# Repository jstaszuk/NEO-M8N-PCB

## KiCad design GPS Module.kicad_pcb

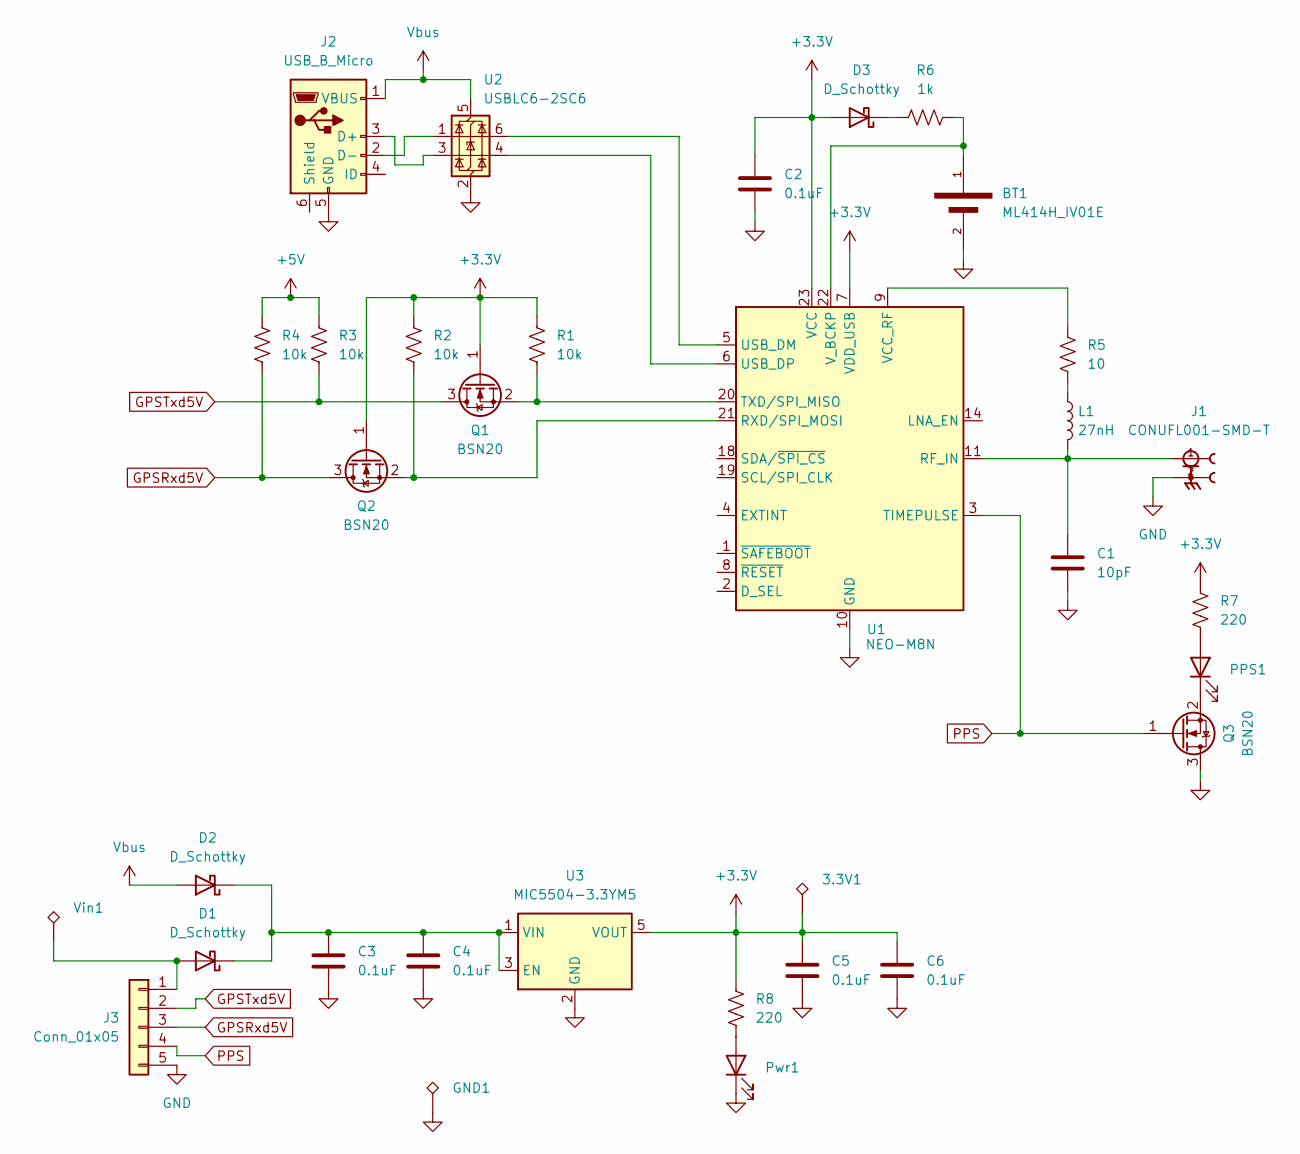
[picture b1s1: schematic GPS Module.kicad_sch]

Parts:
3.3V1: TestPoint_Alt; TestPoint_Pad_D1.0mm
BT1: ML414H_IV01E; SEIKO_ML414H_IV01E
C1: 10pF; C_0603_1608Metric; Part Number CC0603JRNPO9BN100
C2, C3, C4, C5, C6: 0.1uF; C_0603_1608Metric; Part Number CC0603KRX7R9BB104
D1, D2, D3: D_Schottky; D_0805_2012Metric; Part Number ZHCS400TA
GND1: TestPoint_Alt; TestPoint_Pad_D1.0mm
J1: CONUFL001-SMD-T; LINX_CONUFL001-SMD-T
J2: USB_B_Micro; USB_Micro-B_Amphenol_10118193-0002LF_Horizontal
J3: Conn_01x05; JST_EH_B5B-EH-A_1x05_P2.50mm_Vertical
L1: 27nH; L_0603_1608Metric; Part Number B82496C3270J000
PPS1: LED; LED_0603_1608Metric_Pad1.05x0.95mm_HandSolder; Part Number 150060YS75000
Pwr1: LED; LED_0603_1608Metric_Pad1.05x0.95mm_HandSolder; Part Number 150060GS75000
Q1, Q2, Q3: BSN20; SOT-23
R1, R2, R3, R4: 10k; R_0603_1608Metric; Part Number RC0603FR-0710KL
R5: 10; R_0603_1608Metric; Part Number RC0603FR-07100RL
R6: 1k; R_0603_1608Metric; Part Number RC0603FR-071KL
R7, R8: 220; R_0603_1608Metric; Part Number RC0603FR-07220RL
U1: NEO-M8N; ublox_NEO; Part Number NEO-M8N-0
U2: USBLC6-2SC6; SOT-23-6
U3: MIC5504-3.3YM5; SOT-23-5
Vin1: TestPoint_Alt; TestPoint_Pad_D1.0mm

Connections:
+3.3V: 3.3V1.1, C2.1, C5.1, C6.1, D3.2 (A), Q1.1 (G), Q2.1 (G), R1.1, R2.1, R7.1, R8.1, U1.7 (VDD_USB), U1.23 (VCC), U3.5 (VOUT)
+5V: R3.1, R4.1
GND: BT1.2, C1.2, C2.2, C3.2, C4.2, C5.2, C6.2, GND1.1, J1.2, J2.5 (GND), J3.5, Pwr1.1 (K), Q3.3 (D), U1.10 (GND), U1.12 (GND), U1.13 (GND), U1.24 (GND), U2.2 (GND), U3.2 (GND)
GPSRxd5V: J3.3, Q2.3 (D), R4.2
GPSTxd5V: J3.2, Q1.3 (D), R3.2
unnamed: D1.2 (A), J3.1, Vin1.1
unnamed: C3.1, C4.1, D1.1 (K), D2.1 (K), U3.1 (VIN), U3.3 (EN)
unnamed: D3.1 (K), R6.1
unnamed: J2.3 (D+), U2.3 (I/O2)
unnamed: J2.2 (D-), U2.1 (I/O1)
unnamed: L1.1, R5.2
unnamed: PPS1.2 (A), R7.2
unnamed: PPS1.1 (K), Q3.2 (S)
unnamed: Pwr1.2 (A), R8.2
unnamed: Q1.2 (S), R1.2, U1.20 (TXD/SPI_MISO)
unnamed: Q2.2 (S), R2.2, U1.21 (RXD/SPI_MOSI)
unnamed: C1.1, J1.1, L1.2, U1.11 (RF_IN)
unnamed: U1.5 (USB_DM), U2.6 (I/O1)
unnamed: U1.6 (USB_DP), U2.4 (I/O2)
unnamed: R5.1, U1.9 (VCC_RF)
unnamed: BT1.1, R6.2, U1.22 (V_BCKP)
PPS: J3.4, Q3.1 (G), U1.3 (TIMEPULSE)
Vbus: D2.2 (A), J2.1 (VBUS), U2.5 (VBUS)

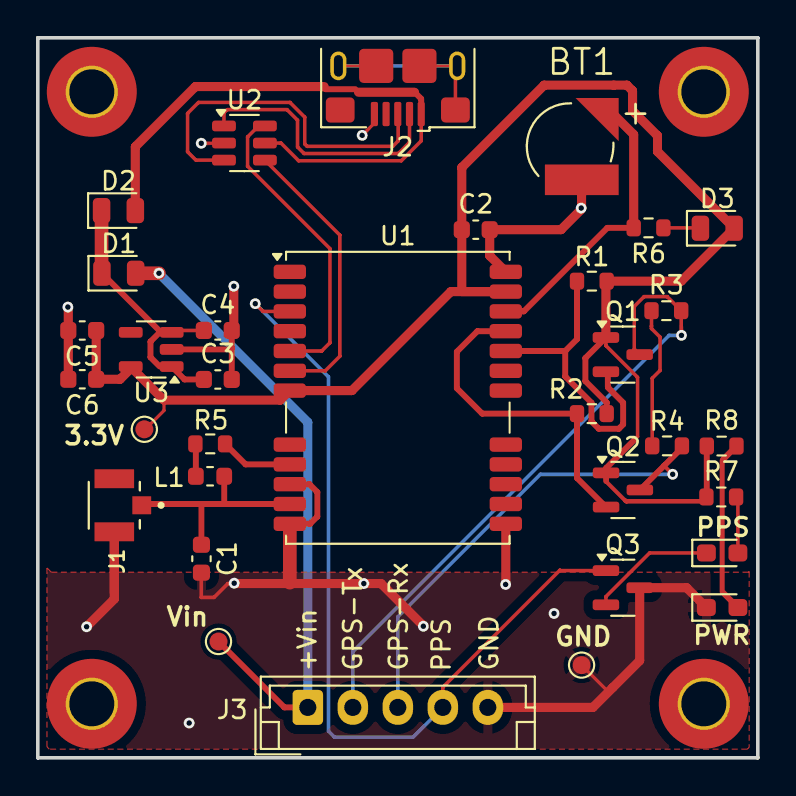
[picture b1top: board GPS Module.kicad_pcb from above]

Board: 2 copper layers, 40.0 x 40.0 mm, 33 parts (0 on the bottom side), 23 nets.
